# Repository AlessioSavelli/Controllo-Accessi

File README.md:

# Controllo Accessi  
 Controllo Accessi realizzato con arduino mkr 1010 e visual studio.

In questa sezione troverai tutti i sorgenti Hardware, Software e Firmware per creare e utilizzare il tuo allarmino.

I Firmware disponibili per Arduino MKR 1010 sono:
<table class="tg">
<thead>
  <tr>
    <th class="tg-0pky">Firmware</th>
  </tr>
</thead>
<tbody>
  <tr>
    <td class="tg-0pky">V1.0</td>
  </tr>
</tbody>
</table>
  
I Software disponibili :
  <table class="tg">
<thead>
  <tr>
    <th class="tg-0lax">Software</th>
    <th class="tg-0pky">Testato su</th>
  </tr>
</thead>
<tbody>
  <tr>
    <td class="tg-0lax">V1.0</td>
    <td class="tg-0pky">Win10 64-bit, Win 11 64-bit</td>
  </tr>
</tbody>
</table>
  
Gli Hardware disponibili :
<table class="tg">
<thead>
  <tr>
    <td class="tg-0lax">Controllo Accessi Main Board</td>
    <td class="tg-0pky">Interfaccia di scrittura badge con Arduino Mini</td>
  </tr>
</thead>
</table>

<a href="https://github.com/AlessioSavelli">Datasheet non acnora disponibile.</a>
----------------------------------------------------------
Licenza MIT
Copyright (c) 2022 Alessio Savelli

Con la presente si concede, a chiunque ottenga una copia di questo software e dei file di documentazione associati (il "Software"), l'autorizzazione a usare gratuitamente il Software senza alcuna limitazione, compresi i diritti di usare, copiare, modificare, unire, pubblicare, distribuire, cedere in sottolicenza e/o vendere copie del Software, nonché di permettere ai soggetti cui il Software è fornito di fare altrettanto, alle seguenti condizioni:

L'avviso di copyright indicato sopra e questo avviso di autorizzazione devono essere inclusi in ogni copia o parte sostanziale del Software.

IL SOFTWARE VIENE FORNITO "COSÌ COM'È", SENZA GARANZIE DI ALCUN TIPO, ESPLICITE O IMPLICITE, IVI INCLUSE, IN VIA ESEMPLIFICATIVA, LE GARANZIE DI COMMERCIABILITÀ, IDONEITÀ A UN FINE PARTICOLARE E NON VIOLAZIONE DEI DIRITTI ALTRUI. IN NESSUN CASO GLI AUTORI O I TITOLARI DEL COPYRIGHT SARANNO RESPONSABILI PER QUALSIASI RECLAMO, DANNO O ALTRO TIPO DI RESPONSABILITÀ, A SEGUITO DI AZIONE CONTRATTUALE, ILLECITO O ALTRO, DERIVANTE DA O IN CONNESSIONE AL SOFTWARE, AL SUO UTILIZZO O AD ALTRE OPERAZIONI CON LO STESSO.
--------------------------------------------------------------
Licenza MIT
Copyright (c) 2022 Alessio Savelli

Con la presente si concede, a chiunque ottenga una copia di questo hardware e dei file di documentazione associati (all "Hardware"), l'autorizzazione a usare gratuitamente l'hardware senza alcuna limitazione, compresi i diritti di usare, copiare, modificare, unire, pubblicare, distribuire, cedere in sottolicenza e/o vendere copie dell'hardware, nonché di permettere ai soggetti il cui hardware è fornito di fare altrettanto, alle seguenti condizioni:

L'avviso di copyright indicato sopra e questo avviso di autorizzazione devono essere inclusi in ogni copia o parte sostanziale dell'hardware.

L'HARDWARE VIENE FORNITO "COSÌ COM'È", SENZA GARANZIE DI ALCUN TIPO, ESPLICITE O IMPLICITE, IVI INCLUSE, IN VIA ESEMPLIFICATIVA, LE GARANZIE DI COMMERCIABILITÀ, IDONEITÀ A UN FINE PARTICOLARE E NON VIOLAZIONE DEI DIRITTI ALTRUI. IN NESSUN CASO GLI AUTORI O I TITOLARI DEL COPYRIGHT SARANNO RESPONSABILI PER QUALSIASI RECLAMO, DANNO O ALTRO TIPO DI RESPONSABILITÀ, A SEGUITO DI AZIONE CONTRATTUALE, ILLECITO O ALTRO, DERIVANTE DA O IN CONNESSIONE DELL'HARDWARE, AL SUO UTILIZZO O AD ALTRE OPERAZIONI CON LO STESSO.

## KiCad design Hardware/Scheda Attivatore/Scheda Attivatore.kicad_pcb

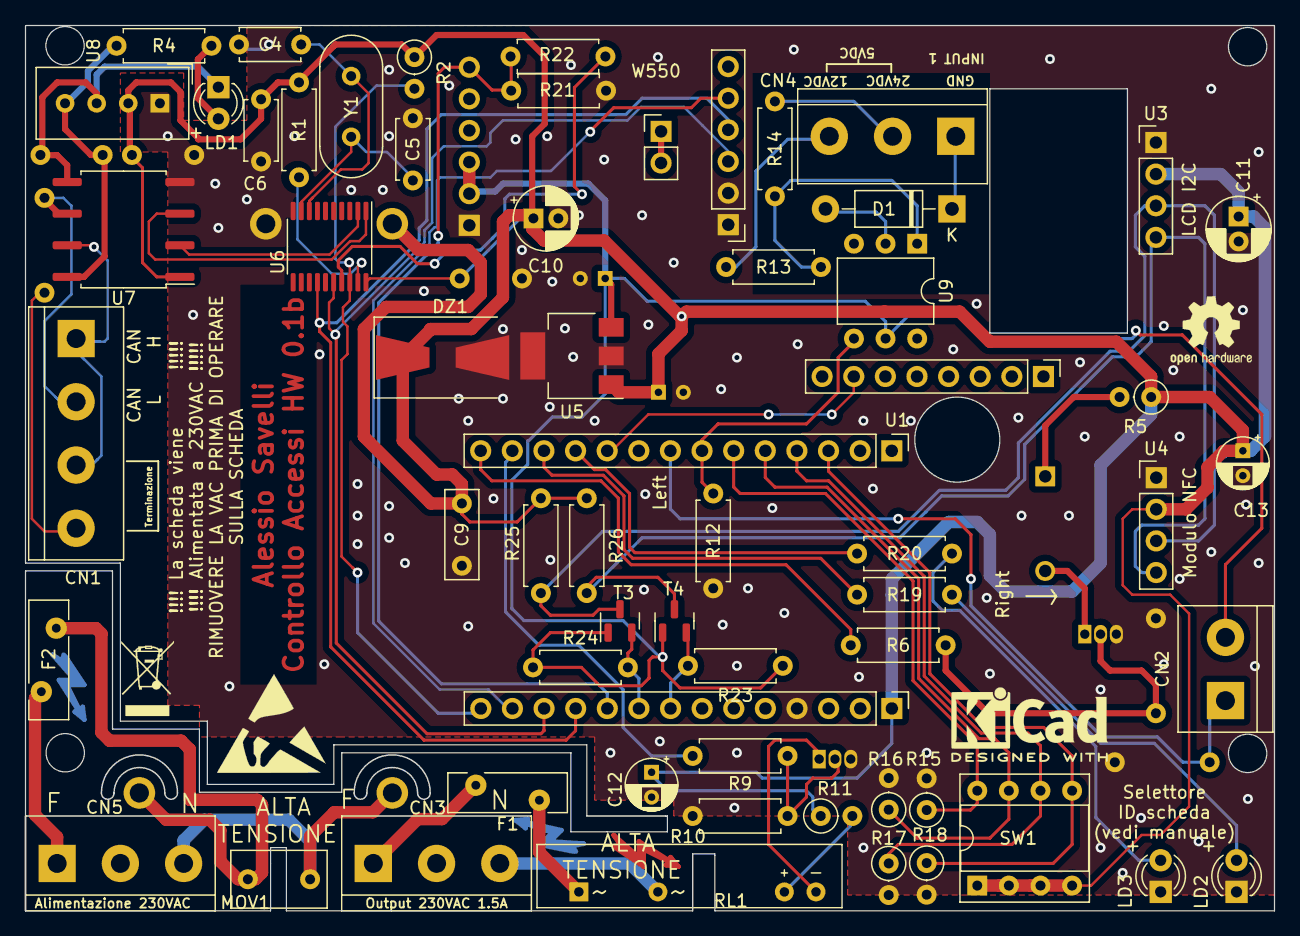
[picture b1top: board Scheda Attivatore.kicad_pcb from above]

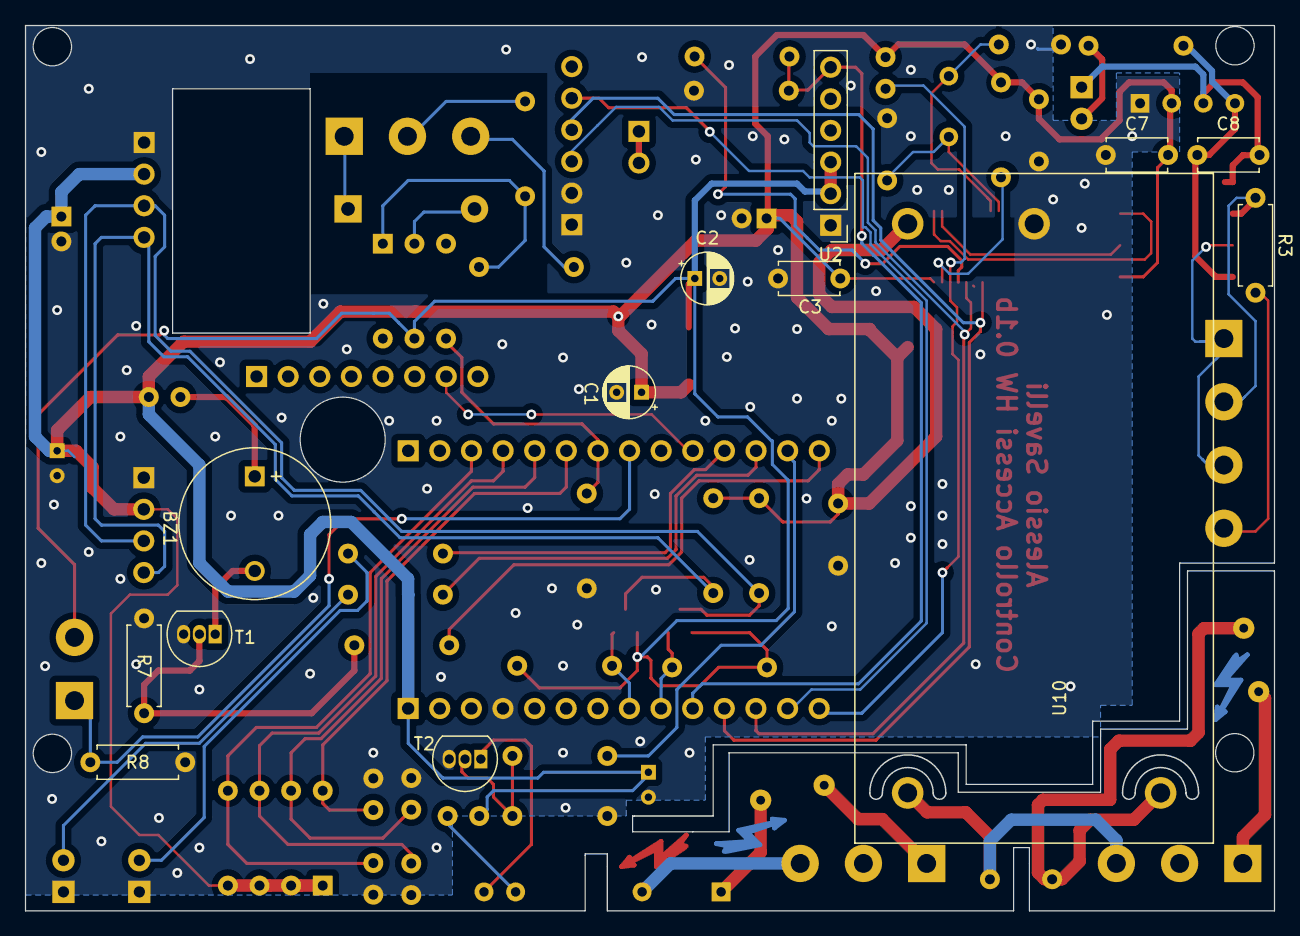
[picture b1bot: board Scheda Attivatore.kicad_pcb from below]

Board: 2 copper layers, 100.3 x 71.1 mm, 74 parts (13 on the bottom side), 55 nets.

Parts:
BZ1: Buzzer; MagneticBuzzer_ProSignal_ABI-010-RC
C1, C2: 1uF; CP_Radial_D4.0mm_P2.00mm
C3, C6, C7, C8: 100nF; C_Disc_D4.7mm_W2.5mm_P5.00mm
C4, C5: 22pF; C_Disc_D4.7mm_W2.5mm_P5.00mm
C9: 1uF 50V; C_Disc_D7.0mm_W2.5mm_P5.00mm
C10, C11: 100uF; CP_Radial_D5.0mm_P2.00mm
C12, C13: 10uF; CP_Radial_D4.0mm_P2.00mm
CN1: CAN_OUT; TerminalBlock_bornier-4_P5.08mm
CN2: Tamper; TerminalBlock_bornier-2_P5.08mm
CN3: Rele' AC; TerminalBlock_bornier-3_P5.08mm
CN4: INPUT; TerminalBlock_bornier-3_P5.08mm
CN5: Supply AC; TerminalBlock_bornier-3_P5.08mm
D1: 1N4007; D_DO-41_SOD81_P10.16mm_Horizontal
DZ1: SMBJ7.0A; D_SMB-SMC_Universal_Handsoldering
F1, F2: 2A; Fuse_Bourns_MF-RHT200
LD1, LD2: Verde; LED_D3.0mm
LD3: Rosso; LED_D3.0mm
MOV1: S14K300; C_Disc_D7.5mm_W4.4mm_P5.00mm
R1: 100k; R_Axial_DIN0207_L6.3mm_D2.5mm_P7.62mm_Horizontal
R2, R15, R16, R17, R18: 100k; R_Axial_DIN0207_L6.3mm_D2.5mm_P2.54mm_Vertical
R3: 120; R_Axial_DIN0207_L6.3mm_D2.5mm_P7.62mm_Horizontal
R4, R6, R9, R19, R20, R22: 470; R_Axial_DIN0207_L6.3mm_D2.5mm_P7.62mm_Horizontal
R5: 120; R_Axial_DIN0207_L6.3mm_D2.5mm_P2.54mm_Vertical
R7, R8, R10, R12: 100K; R_Axial_DIN0207_L6.3mm_D2.5mm_P7.62mm_Horizontal
R11: 330; R_Axial_DIN0207_L6.3mm_D2.5mm_P2.54mm_Vertical
R13: 1.2K; R_Axial_DIN0207_L6.3mm_D2.5mm_P7.62mm_Horizontal
R14: 2.7K; R_Axial_DIN0207_L6.3mm_D2.5mm_P7.62mm_Horizontal
R21: 1K; R_Axial_DIN0207_L6.3mm_D2.5mm_P7.62mm_Horizontal
R23, R24, R25, R26: 10K; R_Axial_DIN0207_L6.3mm_D2.5mm_P7.62mm_Horizontal
RL1: G3MB-20P; G3MB
SW1: DIP x04; DIP-8_W7.62mm_Socket
T1, T2: BC546; TO-92_Inline
T3, T4: BSS123; SOT-23
U1: Left; PinHeader_1x14_P2.54mm_Vertical
U1_1: Right; PinHeader_1x14_P2.54mm_Vertical
U2: W5500; PinHeader_1x06_P2.54mm_Vertical
U2_1: W550; PinHeader_1x06_P2.54mm_Vertical
U3: I2C LCD; PinHeader_1x04_P2.54mm_Vertical
U3_1: Retro illuminazione LCD; PinHeader_1x02_P2.54mm_Vertical
U4: Modulo NFC; PinHeader_1x04_P2.54mm_Vertical
U4_1: Modulo NFC; PinHeader_1x08_P2.54mm_Vertical
U5: TC1262-25; SOT-223-3_TabPin2
U6: MCP2515-xST; TSSOP-20_4.4x6.5mm_P0.65mm
U7: ISO1050DUB; SOP-8_6.62x9.15mm_P2.54mm
U8: ROE 5V-5V; Aosong_DHT11_5.5x12.0_P2.54mm
U9: 4N25; DIP-6_W7.62mm
U10: AC-DC; LDE10-20Bxx
Y1: 8MHz; Crystal_HC49-4H_Vertical

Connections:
+3.3V: C2.1, CN2.2, R23.1, R24.1, T3.1 (G), T4.1 (G), U2.2, U2.3, U5.3 (VO), U9.5
+5C: C8.1, R4.1, U7.8 (VCC2), U8.4 (+Vout)
+5V: C1.1, C3.2, C6.2, C7.2, C9.2, C10.1, C11.1, C12.1, C13.1, DZ1.1 (K), R1.1, R2.1, R5.1, R11.1, R25.1, R26.1, SW1.1, SW1.2, SW1.3, SW1.4, U1_1.1, U3.2, U4.2, U5.1 (VI), U6.20 (VDD), U7.1 (VCC1), U8.2 (+Vin), U10.4
A1: R15.1, SW1.5, U1.3
A2: R16.1, SW1.6, U1.4
A3: R17.1, SW1.7, U1.5
A4: R18.1, SW1.8, U1.6
A5: R12.2, U1.7, U9.4
A6: CN2.1, R8.1, U1.8
BUZZER: R6.1, U1.14
CS_CAN: R2.2, U1_1.14, U6.18 (~CS)
CS_ETH: U1_1.13, U2_1.5
D1: U1.10, U4_1.7
D2: R20.1, U1.11
D3: R19.1, U1.12
D4: R9.1, U1.13
D8: U1_1.12, U2_1.3, U6.16 (SI)
D9: U1_1.11, U2_1.4, U6.14 (SCK)
D10: R21.1, R22.1, U1_1.10, U2.6
D11: R24.2, T3.2 (S), U1_1.9
D12: R23.2, T4.2 (S), U1_1.8
GND: C1.2, C2.2, C3.1, C4.1, C5.2, C6.1, C7.1, C9.1, C10.2, C11.2, C12.2, C13.2, DZ1.2 (A), LD2.1 (K), LD3.1 (K), R7.1, R8.2, R10.1, R12.1, R15.2, R16.2, R17.2, R18.2, R21.2, T1.3 (E), T2.3 (E), U1_1.4, U2.1, U2_1.1, U2_1.2, U3.1, U4.1, U5.2 (GND), U6.10 (VSS), U7.4 (GND1), U8.1 (-Vin), U10.3
GNDD: C8.2, LD1.1 (K), U7.5 (GND2), U8.3 (-Vout)
unnamed: BZ1.2 (+), T1.1 (C)
unnamed: BZ1.1 (-), R5.2
unnamed: CN1.1, CN1.3, U7.7 (CANH)
unnamed: CN1.2, R3.1, U7.6 (CANL)
unnamed: CN1.4, R3.2
unnamed: CN3.1, F1.2
unnamed: CN3.3, RL1.2
unnamed: CN4.1, D1.1 (K)
unnamed: CN4.2, R14.1
unnamed: CN4.3, R13.1
unnamed: CN5.1, F2.1
unnamed: CN5.3, MOV1.2, U10.2
unnamed: D1.2 (A), U9.2
unnamed: F1.1, RL1.1
unnamed: LD1.2 (A), R4.2
unnamed: LD2.2 (A), R19.2
unnamed: LD3.2 (A), R20.2
unnamed: R11.2, RL1.3
unnamed: R13.2, R14.2, U9.1
unnamed: R6.2, R7.2, T1.2 (B)
unnamed: R9.2, R10.2, T2.2 (B)
unnamed: RL1.4, T2.1 (C)
unnamed: U3_1.1, U3_1.2
unnamed: C5.1, U6.9 (OSC1), Y1.1
unnamed: C4.2, U6.8 (OSC2), Y1.2
unnamed: U6.2 (RXCAN), U7.2 (RXD)
unnamed: R22.2, U6.17 (SO)
unnamed: U6.1 (TXCAN), U7.3 (TXD)
unnamed: R1.2, U6.19 (~RESET)
unnamed: F2.2, MOV1.1, U10.1
SCL: R26.2, T4.3 (D), U3.4, U4.4
SDA: R25.2, T3.3 (D), U3.3, U4.3

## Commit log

2023-09-24 Frist Push
    Invio di tutti i file.

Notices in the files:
README.md:
License: MIT License
